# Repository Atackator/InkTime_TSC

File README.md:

InkTime-TSC Project

This project presents the design and development of a low-power, multi-functional smartwatch platform. The system is built around the nRF52840 SoC and integrates an E-paper display, motion sensing capabilities, and optimized power management within a compact PCB tailored for wearable devices.

### Bill of Materials (BOM) - PCB INKTIME

| Cant. | Referințe | Valoare | Capsulă | Descriere | MPN |
|:---:|:---|:---|:---|:---|:---|
| 1 | ANT1 | 2450AT18B100E | ANTC3216 | Antennas 2.45GHz | 2450AT18B100E |
| 4 | C1, C2, C17, C18 | 12pF | 0201 | Generic chip capacitor | - |
| 6 | C29, C30, C31, C32, C37, C38 | 1uF | 0201 | Generic chip capacitor | - |
| 1 | IC1 | BQ25180YBGR | 8-DSBGA | Charger IC Li-Ion | Texas Instruments |
| 1 | IC2 | DRV2605YZFR | 9-DSBGA | Haptic Driver | DRV2605YZFR |
| 1 | IC9 | RT6160AWSC | 15-WLCSP | Buck-Boost Regulator | RT6160AWSC |
| 1 | U1 | NRF52840_QF | AQFN-73 | nRF52840 SoC | - |
| 14 | TP1...TP_VREG | Test Point | TP20R | Test pads | - |

Hardware Overview
1. Core Processing Unit: nRF52840

The nRF52840 System-on-Chip serves as the central controller, chosen for its strong balance between computational performance and low energy consumption.

Main Characteristics:

ARM Cortex-M4F core with floating-point support
Native USB functionality
Flexible GPIO configuration supporting SPI and I2C interfaces

Clocking:

32 MHz external crystal for high-speed operation
32.768 kHz crystal for accurate timekeeping during low-power modes

Wireless Capability:

Integrated 2.4 GHz RF frontend paired with a ceramic antenna for Bluetooth Low Energy (BLE) communication
2. Power Management and Charging

The device includes a carefully designed power architecture to support portable operation.

USB-C Port:

Provides 5V input and data connectivity
Protected against electrostatic discharge using the USBLC6-2SC6Y

Battery Charging and Regulation:

BQ25180 handles LiPo charging and power path management
RT6160 DC/DC converter ensures efficient voltage regulation

Filtering and Stability:

LC filtering network reduces noise and stabilizes supply rails

Battery Monitoring:

MAX17048 fuel gauge communicates via I2C to estimate battery charge level accurately
3. E-Paper Display Module

A 1.54-inch E-paper display is used as the main visual interface, connected through a 24-pin FPC connector.

Driving Mechanism:

A custom boost circuit (using MOSFETs, Schottky diodes, and capacitors) generates the required high voltages

Communication:

SPI interface with dedicated control signals: DC (Data/Command), RST (Reset), and BUSY

Design Motivation:

The display retains the image without continuous power, making it ideal for always-on wearable applications
4. Motion Sensing and Haptic Feedback

IMU Sensor:

BMA421 accelerometer used for motion tracking
I2C communication interface
Interrupt pins (INT1, INT2) allow the MCU to wake on movement or gesture detection

Haptic System:

DRV2605 driver controls vibration feedback
Offloads waveform generation from the MCU for efficient operation
5. User Interface and Debugging

Buttons:

Three physical buttons (Up, Enter, Down) connected to GPIOs for navigation

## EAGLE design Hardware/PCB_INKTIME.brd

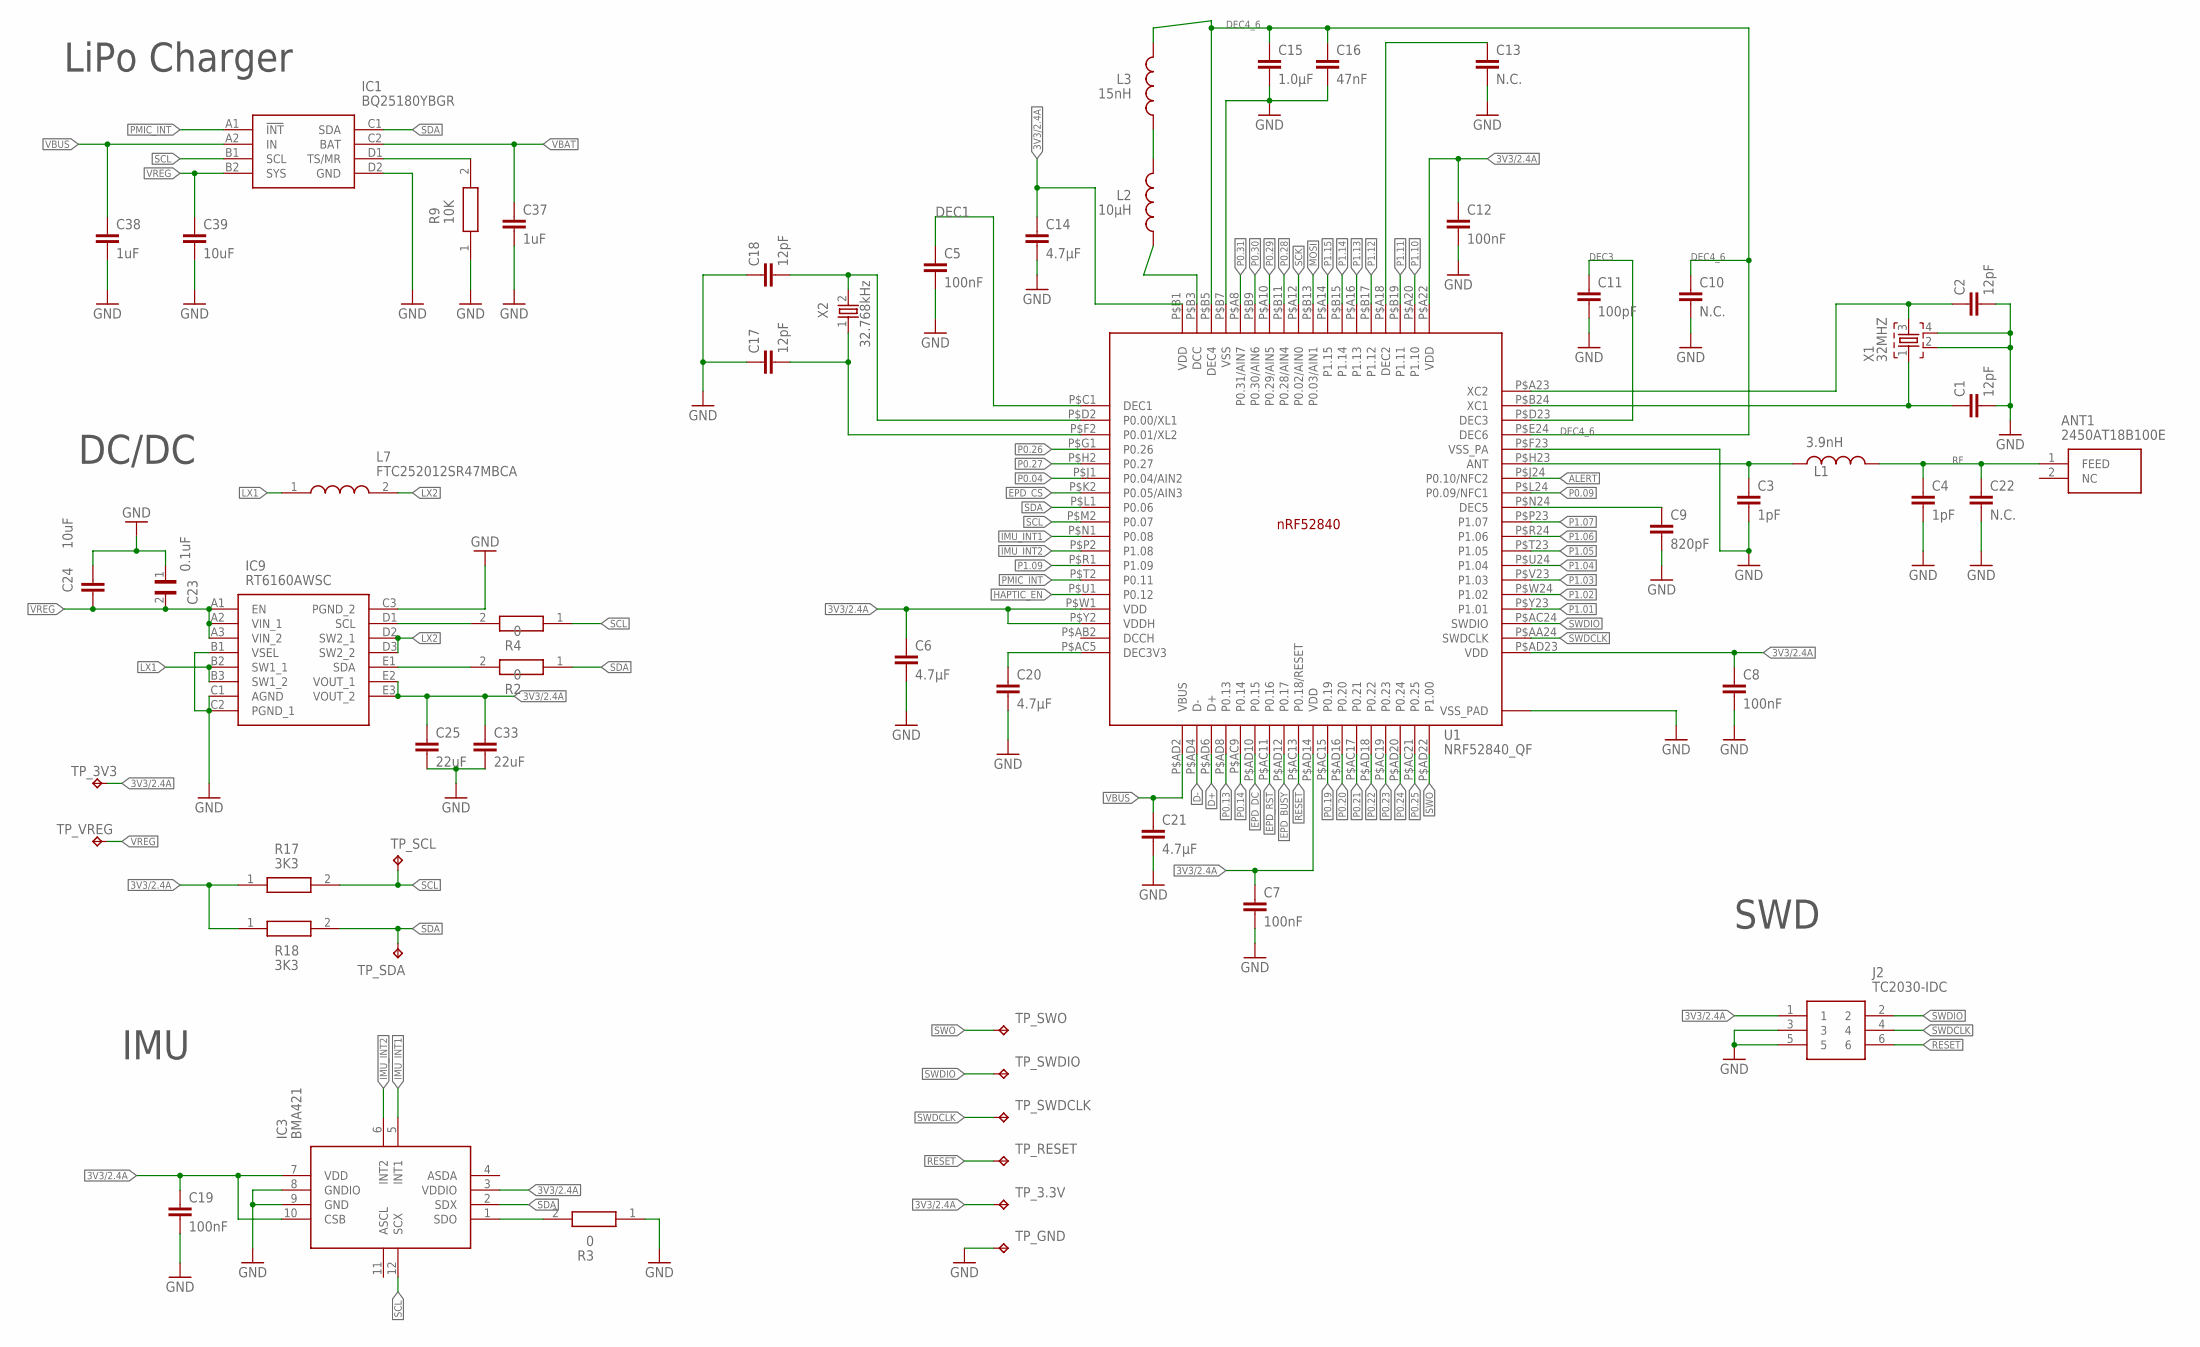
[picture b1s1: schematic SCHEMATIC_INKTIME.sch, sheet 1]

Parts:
ANT1: 2450AT18B100E; 2450AT18B100E_ANTC3216X140N
C1, C2, C17, C18: 12pF; NORDIC_NRF_3_RESC0201_L
C3, C4: 1pF; NORDIC_NRF_3_RESC0201_L
C5, C7, C8, C12, C19: 100nF; NORDIC_NRF_3_RESC0201_L
C6, C14, C20, C21: 4.7µF; NORDIC_NRF_3_RESC0402_L
C9: 820pF; NORDIC_NRF_3_RESC0201_L
C10, C13, C22: N.C.; NORDIC_NRF_3_RESC0201_L
C11: 100pF; NORDIC_NRF_3_RESC0201_L
C15: 1.0µF; NORDIC_NRF_3_RESC0402_L
C16: 47nF; NORDIC_NRF_3_RESC0201_L
C23: 0.1uF; GRM011R60J152KE01L_2_CAPC0201X13N
C24, C39: 10uF; NORDIC_NRF_3_RESC0402_L
C25, C33: 22uF; NORDIC_NRF_3_RESC0402_L
C37, C38: 1uF; NORDIC_NRF_3_RESC0402_L
IC1: BQ25180YBGR; BQ25180YBGR_BGA8C40P2X4_100X155X50
IC3: BMA421; BMA423_BMA423
IC9: RT6160AWSC; RT6160AWSC_BGA15C40P3X5_140X230X60
J2: TC2030-IDC; TC2030-IDC_TC2030IDC
L1: 3.9nH; NORDIC_NRF_2_RESC0402_L
L2: 10µH; NORDIC_NRF_2_RESC0402_L
L3: 15nH; NORDIC_NRF_2_RESC0402_L
L7: FTC252012SR47MBCA; MLP2016SR47MT0S1_INDC2016X100N
R2, R3, R4: 0; CPF0201D7K68C1_0201
R9: 10K; CPF0201D7K68C1_0201
R17, R18: 3K3; CPF0201D7K68C1_0201
TP_3.3V, TP_3V3: HECTOR_WATCH_1_TPTP20R; HECTOR_WATCH_1_TP20R
TP_GND: HECTOR_WATCH_1_TPTP20R; HECTOR_WATCH_1_TP20R
TP_RESET: HECTOR_WATCH_1_TPTP20R; HECTOR_WATCH_1_TP20R
TP_SCL: HECTOR_WATCH_1_TPTP20R; HECTOR_WATCH_1_TP20R
TP_SDA: HECTOR_WATCH_1_TPTP20R; HECTOR_WATCH_1_TP20R
TP_SWDCLK: HECTOR_WATCH_1_TPTP20R; HECTOR_WATCH_1_TP20R
TP_SWDIO: HECTOR_WATCH_1_TPTP20R; HECTOR_WATCH_1_TP20R
TP_SWO: HECTOR_WATCH_1_TPTP20R; HECTOR_WATCH_1_TP20R
TP_VREG: HECTOR_WATCH_1_TPTP20R; HECTOR_WATCH_1_TP20R
U1: NRF52840_QF; NORDIC_NRF_4_AQFN50P700X700X85_HS-74N
X1: 32MHZ; NORDIC_NRF_BT-XTAL_2016_N
X2: 32.768kHz; NORDIC_NRF_1_XTAL_3215_N

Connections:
3V3/2.4A: C6.1, C7.1, C8.1, C12.1, C14.1, C19.1, C25.1, C33.1, IC3.3 (VDDIO), IC3.7 (VDD), IC3.10 (CSB), IC9.E2 (VOUT_1), IC9.E3 (VOUT_2), J2.1, R17.1, R18.1, TP_3.3V.TP, TP_3V3.TP, U1.P$A22 (VDD), U1.P$AD14 (VDD), U1.P$AD23 (VDD), U1.P$B1 (VDD), U1.P$W1 (VDD), U1.P$Y2 (VDDH); also elsewhere on the board
ALERT: U1.P$J24 (P0.10/NFC2); also elsewhere on the board
D+: U1.P$AD6 (D+); also elsewhere on the board
D-: U1.P$AD4 (D-); also elsewhere on the board
DEC1: C5.1, U1.P$C1 (DEC1)
DEC3: C11.1, U1.P$D23 (DEC3)
DEC4_6: C10.1, C15.1, C16.1, L3.2, U1.P$B5 (DEC4), U1.P$E24 (DEC6)
EPD_BUSY: U1.P$AD12 (P0.17); also elsewhere on the board
EPD_CS: U1.P$K2 (P0.05/AIN3); also elsewhere on the board
EPD_DC: U1.P$AD10 (P0.15); also elsewhere on the board
EPD_RST: U1.P$AC11 (P0.16); also elsewhere on the board
GND: C1.2, C2.2, C3.2, C4.2, C5.2, C6.2, C7.2, C8.2, C9.2, C10.2, C11.2, C12.2, C13.2, C14.2, C15.2, C16.2, C17.1, C18.1, C19.2, C20.2, C21.2, C22.2, C23.1, C24.1, C25.2, C33.2, C37.2, C38.2, C39.2, IC1.D2 (GND), IC3.8 (GNDIO), IC3.9 (GND), IC9.B1 (VSEL), IC9.C1 (AGND), IC9.C2 (PGND_1), IC9.C3 (PGND_2), J2.3, J2.5, R3.1, R9.1, TP_GND.TP, U1.P$74 (VSS_PAD), U1.P$75 (VSS_PAD), U1.P$76 (VSS_PAD), U1.P$77 (VSS_PAD), U1.P$78 (VSS_PAD), U1.P$79 (VSS_PAD), U1.P$80 (VSS_PAD), U1.P$81 (VSS_PAD), U1.P$82 (VSS_PAD), U1.P$83 (VSS_PAD), U1.P$84 (VSS_PAD), U1.P$85 (VSS_PAD), U1.P$86 (VSS_PAD), U1.P$87 (VSS_PAD), U1.P$88 (VSS_PAD), U1.P$89 (VSS_PAD), U1.P$90 (VSS_PAD), U1.P$B7 (VSS), U1.P$F23 (VSS_PA), X1.2, X1.4; also elsewhere on the board
HAPTIC_EN: U1.P$U1 (P0.12); also elsewhere on the board
IMU_INT1: IC3.5 (INT1), U1.P$N1 (P0.08)
IMU_INT2: IC3.6 (INT2), U1.P$P2 (P1.08)
LX1: IC9.B2 (SW1_1), IC9.B3 (SW1_2), L7.1
LX2: IC9.D2 (SW2_1), IC9.D3 (SW2_2), L7.2
MOSI: U1.P$B13 (P0.03/AIN1); also elsewhere on the board
unnamed: IC1.D1 (TS/MR), R9.2
unnamed: C18.2, U1.P$D2 (P0.00/XL1), X2.2
unnamed: C1.1, U1.P$B24 (XC1), X1.1
unnamed: C2.1, U1.P$A23 (XC2), X1.3
unnamed: C17.2, U1.P$F2 (P0.01/XL2), X2.1
unnamed: L2.2, L3.1
unnamed: L2.1, U1.P$B3 (DCC)
unnamed: C9.1, U1.P$N24 (DEC5)
unnamed: C13.1, U1.P$A18 (DEC2)
unnamed: C3.1, L1.1, U1.P$H23 (ANT)
unnamed: C20.1, U1.P$AC5 (DEC3V3)
unnamed 35: IC3.1 (SDO), R3.2; also elsewhere on the board
unnamed: IC9.E1 (SDA), R2.2
unnamed: IC9.D1 (SCL), R4.2
P0.04: U1.P$J1 (P0.04/AIN2)
P0.09: U1.P$L24 (P0.09/NFC1)
P0.13: U1.P$AD8 (P0.13); also elsewhere on the board
P0.14: U1.P$AC9 (P0.14); also elsewhere on the board
P0.19: U1.P$AC15 (P0.19)
P0.20: U1.P$AD16 (P0.20)
P0.21: U1.P$AC17 (P0.21)
P0.22: U1.P$AD18 (P0.22)
P0.23: U1.P$AC19 (P0.23)
P0.24: U1.P$AD20 (P0.24)
P0.25: U1.P$AC21 (P0.25)
P0.26: U1.P$G1 (P0.26)
P0.27: U1.P$H2 (P0.27)
P0.28: U1.P$B11 (P0.28/AIN4)
P0.29: U1.P$A10 (P0.29/AIN5)
P0.30: U1.P$B9 (P0.30/AIN6)
P0.31: U1.P$A8 (P0.31/AIN7)
P1.01: U1.P$Y23 (P1.01); also elsewhere on the board
P1.02: U1.P$W24 (P1.02); also elsewhere on the board
P1.03: U1.P$V23 (P1.03)
P1.04: U1.P$U24 (P1.04)
P1.05: U1.P$T23 (P1.05)
P1.06: U1.P$R24 (P1.06)
P1.07: U1.P$P23 (P1.07)
P1.09: U1.P$R1 (P1.09)
P1.10: U1.P$A20 (P1.10)
P1.11: U1.P$B19 (P1.11)
P1.12: U1.P$B17 (P1.12)
P1.13: U1.P$A16 (P1.13)
P1.14: U1.P$B15 (P1.14)
P1.15: U1.P$A14 (P1.15)
PMIC_INT: IC1.A1 (!INT), U1.P$T2 (P0.11)
RESET: J2.6, TP_RESET.TP, U1.P$AC13 (P0.18/RESET)
RF: ANT1.1 (FEED), C4.1, C22.1, L1.2
SCK: U1.P$A12 (P0.02/AIN0); also elsewhere on the board
SCL: IC1.B1 (SCL), IC3.12 (SCX), R4.1, R17.2, TP_SCL.TP, U1.P$M2 (P0.07); also elsewhere on the board
SDA: IC1.C1 (SDA), IC3.2 (SDX), R2.1, R18.2, TP_SDA.TP, U1.P$L1 (P0.06); also elsewhere on the board
SWDCLK: J2.4, TP_SWDCLK.TP, U1.P$AA24 (SWDCLK)
SWDIO: J2.2, TP_SWDIO.TP, U1.P$AC24 (SWDIO)
SWO: TP_SWO.TP, U1.P$AD22 (P1.00)
VBAT: C37.1, IC1.C2 (BAT); also elsewhere on the board
VBUS: C21.1, C38.1, IC1.A2 (IN), U1.P$AD2 (VBUS); also elsewhere on the board
VREG: C23.2, C24.2, C39.1, IC1.B2 (SYS), IC9.A1 (EN), IC9.A2 (VIN_1), IC9.A3 (VIN_2), TP_VREG.TP

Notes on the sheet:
LiPo Charger
DC/DC
IMU
SWD

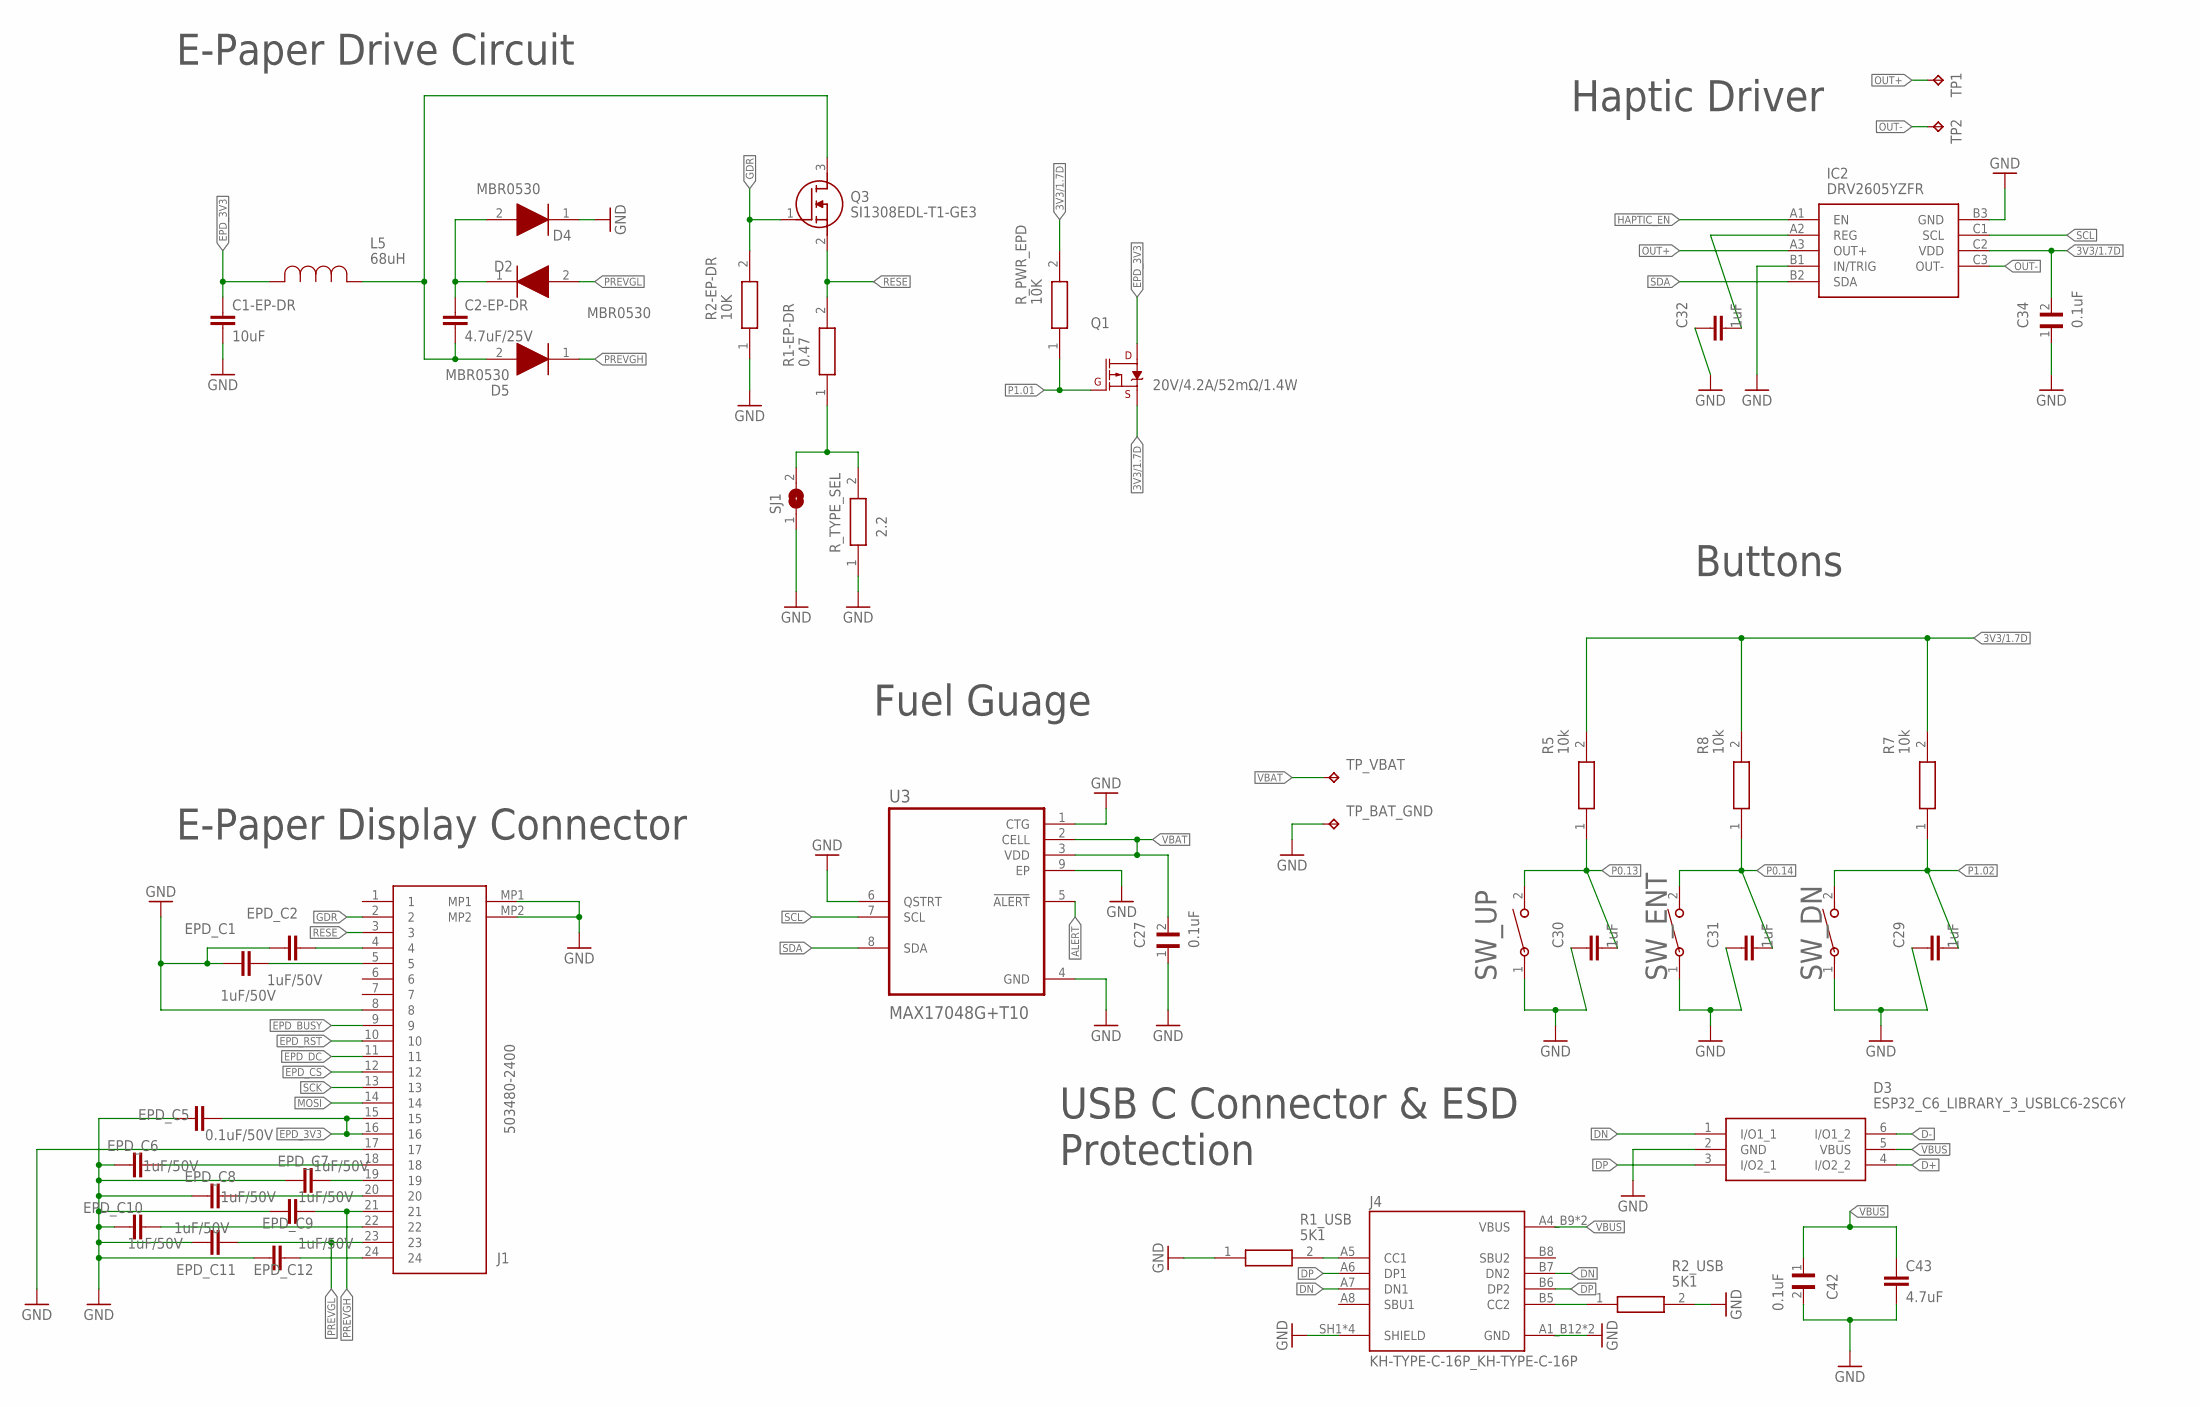
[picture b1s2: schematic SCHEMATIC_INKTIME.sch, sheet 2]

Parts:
C1-EP-DR: 10uF; NORDIC_NRF_3_RESC0402_L
C2-EP-DR: 4.7uF/25V; NORDIC_NRF_3_RESC0402_L
C27, C34, C42: 0.1uF; GRM011R60J152KE01L_2_CAPC0201X13N
C29, C30, C31, C32: 1uF; NORDIC_NRF_3_RESC0402_L
C43: 4.7uF; NORDIC_NRF_3_RESC0402_L
D2, D4, D5: MBR0530; ESP32_C6_LIBRARY_5_SOD3716X135N
D3: ESP32_C6_LIBRARY_3_USBLC6-2SC6Y; ESP32_C6_LIBRARY_3_SOT95P280X145-6N
EPD_C1, EPD_C2, EPD_C6, EPD_C7, EPD_C8, EPD_C9, EPD_C10, EPD_C11, EPD_C12: 1uF/50V; NORDIC_NRF_3_RESC0402_L
EPD_C5: 0.1uF/50V; NORDIC_NRF_3_RESC0201_L
IC2: DRV2605YZFR; DRV2605YZFR_BGA9C50P3X3_144X144X62
J1: 503480-2400; 503480-2400_5034802400
J4: KH-TYPE-C-16P_KH-TYPE-C-16P; KH-TYPE-C-16P_KINGHELM_KH-TYPE-C-16P
L5: 68uH; ESP32_C6_LIBRARY_2_IND_4828-WE-TPC_WRE
Q1: 20V/4.2A/52mΩ/1.4W; ESP32_C6_LIBRARY_4_ESP32_C6_LIBRARY_4_ESP32_C6_LIBRARY_4_ES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
Q3: SI1308EDL-T1-GE3; ESP32_C6_LIBRARY_6_SOT65P210X110-3N
R1-EP-DR: 0.47; CPF0201D7K68C1_0201
R1_USB, R2_USB: 5K1; CPF0201D7K68C1_0201
R2-EP-DR: 10K; CPF0201D7K68C1_0201
R5, R7, R8: 10k; CPF0201D7K68C1_0201
R_PWR_EPD: 10K; CPF0201D7K68C1_0201
R_TYPE_SEL: 2.2; CPF0201D7K68C1_0201
SJ1: ESP32_C6_LIBRARY_7_JUMPER_SJ
SW_DN: 2025-10-22_07-23-44_LIBRARY_EVP-AKE31ASW_EVP-AKE3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; 2025-10-22_07-23-44_LIBRARY_SW_EVP-AKE31A_PAN
SW_ENT: 2025-10-22_07-23-44_LIBRARY_EVP-AKE31ASW_EVP-AKE3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; 2025-10-22_07-23-44_LIBRARY_SW_EVP-AKE31A_PAN
SW_UP: 2025-10-22_07-23-44_LIBRARY_EVP-AKE31ASW_EVP-AKE3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; 2025-10-22_07-23-44_LIBRARY_SW_EVP-AKE31A_PAN
TP1, TP2: HECTOR_WATCH_1_TPTP20R; HECTOR_WATCH_1_TP20R
TP_BAT_GND: HECTOR_WATCH_1_TPTP20R; HECTOR_WATCH_1_TP20R
TP_VBAT: HECTOR_WATCH_1_TPTP20R; HECTOR_WATCH_1_TP20R
U3: MAX17048G+T10; ESP32_C6_LIBRARY_SON50P200X200X80-9N

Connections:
3V3/1.7D: C34.2, IC2.C2 (VDD), Q1.2 (S), R5.2, R7.2, R8.2, R_PWR_EPD.2
ALERT: U3.5 (!ALERT); also elsewhere on the board
D+: D3.4 (I/O2_2); also elsewhere on the board
D-: D3.6 (I/O1_2); also elsewhere on the board
DN: D3.1 (I/O1_1), J4.A7 (DN1), J4.B7 (DN2)
DP: D3.3 (I/O2_1), J4.A6 (DP1), J4.B6 (DP2)
EPD_3V3: C1-EP-DR.1, EPD_C5.2, J1.15, J1.16, L5.2, Q1.3 (D); also elsewhere on the board
EPD_BUSY: J1.9; also elsewhere on the board
EPD_CS: J1.12; also elsewhere on the board
EPD_DC: J1.11; also elsewhere on the board
EPD_RST: J1.10; also elsewhere on the board
GDR: J1.2, Q3.1 (G), R2-EP-DR.2
GND: C1-EP-DR.2, C27.1, C29.1, C30.1, C31.1, C32.1, C34.1, C42.2, C43.2, D3.2 (GND), D4.1 (K), EPD_C1.1, EPD_C2.1, EPD_C5.1, EPD_C6.1, EPD_C7.1, EPD_C8.1, EPD_C9.1, EPD_C10.1, EPD_C11.1, EPD_C12.1, IC2.B1 (IN/TRIG), IC2.B3 (GND), J1.8, J1.17, J1.MP1, J1.MP2, J4.A1_B12 (GND), J4.A12_B1 (GND), J4.SH1 (SHIELD), J4.SH2 (SHIELD), J4.SH3 (SHIELD), J4.SH4 (SHIELD), R1_USB.1, R2-EP-DR.1, R2_USB.2, R_TYPE_SEL.1, SJ1.1, SW_DN.1, SW_ENT.1, SW_UP.1, TP_BAT_GND.TP, U3.1 (CTG), U3.4 (GND), U3.6 (QSTRT), U3.9 (EP); also elsewhere on the board
HAPTIC_EN: IC2.A1 (EN); also elsewhere on the board
MOSI: J1.14; also elsewhere on the board
unnamed: C32.2, IC2.A2 (REG)
unnamed 36: C2-EP-DR.2, D5.2 (A), L5.1, Q3.3 (D); also elsewhere on the board
unnamed: C2-EP-DR.1, D2.1 (K), D4.2 (A)
unnamed: J4.A5 (CC1), R1_USB.2
unnamed: EPD_C2.2, J1.4
unnamed: R1-EP-DR.1, R_TYPE_SEL.2, SJ1.2
unnamed: EPD_C1.2, J1.5
unnamed: J4.B5 (CC2), R2_USB.1
unnamed: EPD_C6.2, J1.18
unnamed: EPD_C7.2, J1.19
unnamed: EPD_C8.2, J1.20
unnamed: EPD_C10.2, J1.22
unnamed: EPD_C12.2, J1.24
OUT+: IC2.A3 (OUT+), TP1.TP
OUT-: IC2.C3 (OUT-), TP2.TP
P0.13: C30.2, R5.1, SW_UP.2; also elsewhere on the board
P0.14: C31.2, R8.1, SW_ENT.2; also elsewhere on the board
P1.01: Q1.1 (G), R_PWR_EPD.1; also elsewhere on the board
P1.02: C29.2, R7.1, SW_DN.2; also elsewhere on the board
PREVGH: D5.1 (K), EPD_C9.2, J1.21
PREVGL: D2.2 (A), EPD_C11.2, J1.23
RESE: J1.3, Q3.2 (S), R1-EP-DR.2
SCK: J1.13; also elsewhere on the board
SCL: IC2.C1 (SCL), U3.7 (SCL); also elsewhere on the board
SDA: IC2.B2 (SDA), U3.8 (SDA); also elsewhere on the board
VBAT: C27.2, TP_VBAT.TP, U3.2 (CELL), U3.3 (VDD); also elsewhere on the board
VBUS: C42.1, C43.1, D3.5 (VBUS), J4.A4_B9 (VBUS), J4.A9_B4 (VBUS); also elsewhere on the board

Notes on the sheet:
E-Paper Drive Circuit
E-Paper Display Connector
Fuel Guage
Buttons
Haptic Driver
USB C Connector & ESD Protection

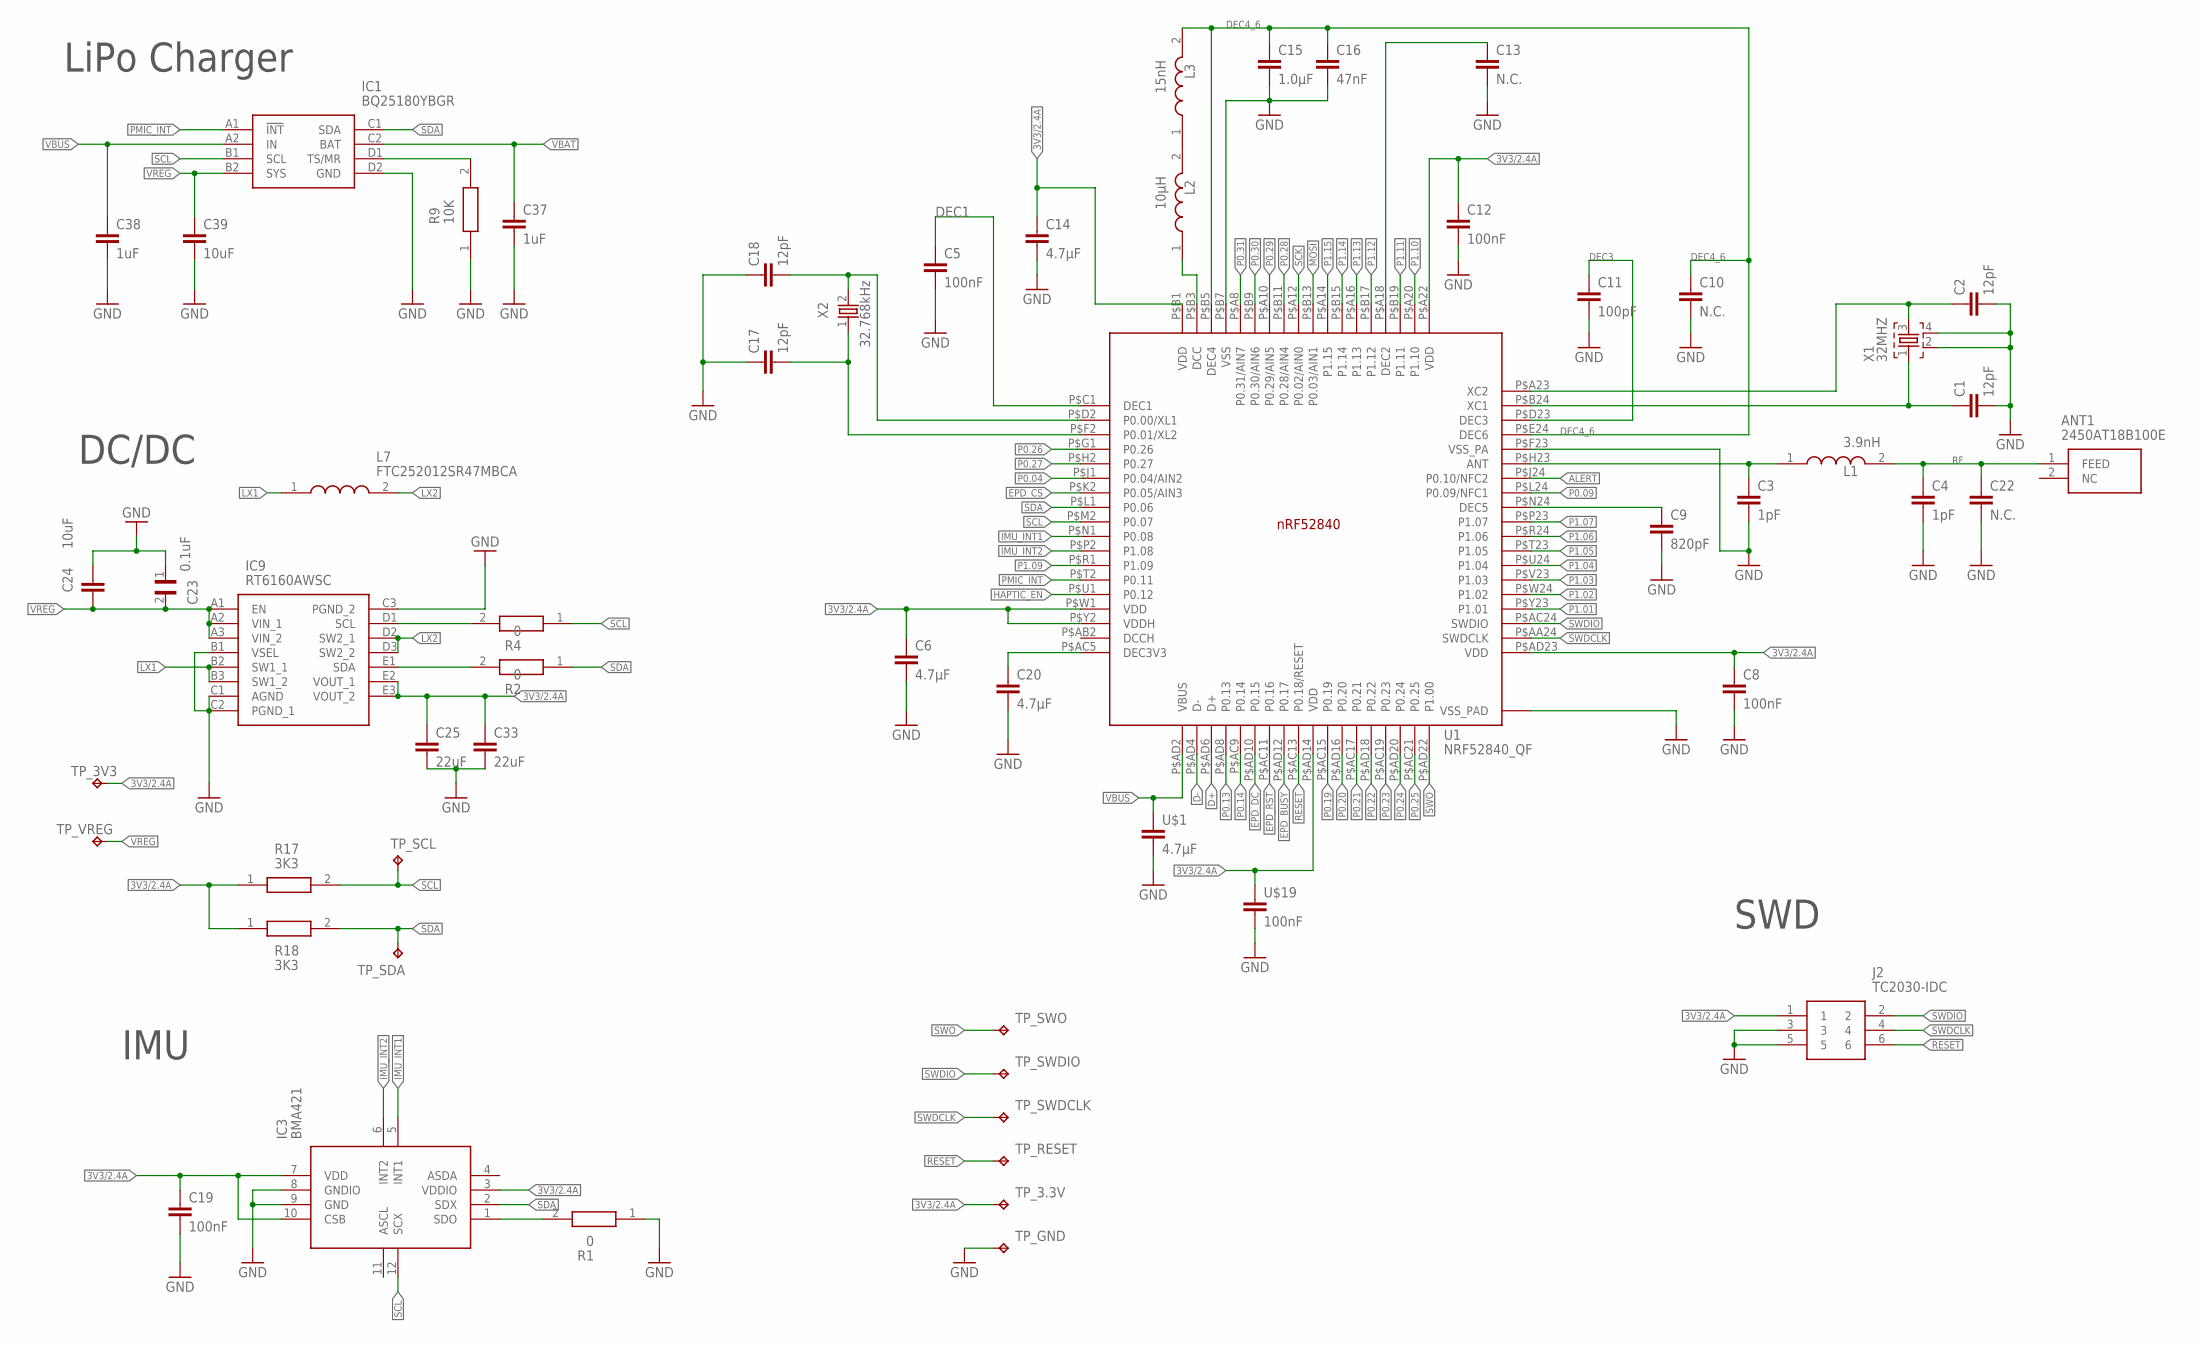
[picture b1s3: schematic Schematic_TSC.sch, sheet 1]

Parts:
ANT1: 2450AT18B100E; 2450AT18B100E_ANTC3216X140N
C1, C2, C17, C18: 12pF; NORDIC_NRF_3_RESC0201_L
C3, C4: 1pF; NORDIC_NRF_3_RESC0201_L
C5, C8, C12, C19: 100nF; NORDIC_NRF_3_RESC0201_L
C6, C14, C20: 4.7µF; NORDIC_NRF_3_RESC0201_L
C9: 820pF; NORDIC_NRF_3_RESC0201_L
C10, C13, C22: N.C.; NORDIC_NRF_3_RESC0201_L
C11: 100pF; NORDIC_NRF_3_RESC0201_L
C15: 1.0µF; NORDIC_NRF_3_RESC0201_L
C16: 47nF; NORDIC_NRF_3_RESC0201_L
C23: 0.1uF; GRM011R60J152KE01L_2_CAPC0201X13N
C24, C39: 10uF; NORDIC_NRF_3_RESC0201_L
C25, C33: 22uF; NORDIC_NRF_3_RESC0201_L
C37, C38: 1uF; NORDIC_NRF_3_RESC0201_L
IC1: BQ25180YBGR; BQ25180YBGR_BGA8C40P2X4_100X155X50
IC3: BMA421; BMA423_BMA423
IC9: RT6160AWSC; RT6160AWSC_BGA15C40P3X5_140X230X60
J2: TC2030-IDC; TC2030-IDC_TC2030IDC
L1: 3.9nH; MLP2016SR47MT0S1_INDC2016X100N
L2: 10µH; MLP2016SR47MT0S1_INDC2016X100N
L3: 15nH; MLP2016SR47MT0S1_INDC2016X100N
L7: FTC252012SR47MBCA; MLP2016SR47MT0S1_INDC2016X100N
R1, R2, R4: 0; CPF0201D7K68C1_0201
R9: 10K; CPF0201D7K68C1_0201
R17, R18: 3K3; CPF0201D7K68C1_0201
TP_3.3V, TP_3V3: HECTOR_WATCH_1_TPTP20R; HECTOR_WATCH_1_TP20R
TP_GND: HECTOR_WATCH_1_TPTP20R; HECTOR_WATCH_1_TP20R
TP_RESET: HECTOR_WATCH_1_TPTP20R; HECTOR_WATCH_1_TP20R
TP_SCL: HECTOR_WATCH_1_TPTP20R; HECTOR_WATCH_1_TP20R
TP_SDA: HECTOR_WATCH_1_TPTP20R; HECTOR_WATCH_1_TP20R
TP_SWDCLK: HECTOR_WATCH_1_TPTP20R; HECTOR_WATCH_1_TP20R
TP_SWDIO: HECTOR_WATCH_1_TPTP20R; HECTOR_WATCH_1_TP20R
TP_SWO: HECTOR_WATCH_1_TPTP20R; HECTOR_WATCH_1_TP20R
TP_VREG: HECTOR_WATCH_1_TPTP20R; HECTOR_WATCH_1_TP20R
U1: NRF52840_QF; NORDIC_NRF_4_AQFN50P700X700X85_HS-74N
U$1: 4.7µF; NORDIC_NRF_3_RESC0201_L
U$19: 100nF; NORDIC_NRF_3_RESC0201_L
X1: 32MHZ; NORDIC_NRF_BT-XTAL_2016_N
X2: 32.768kHz; NORDIC_NRF_1_XTAL_3215_N

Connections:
3V3/2.4A: C6.1, C8.1, C12.1, C14.1, C19.1, C25.1, C33.1, IC3.3 (VDDIO), IC3.7 (VDD), IC3.10 (CSB), IC9.E2 (VOUT_1), IC9.E3 (VOUT_2), J2.1, R17.1, R18.1, TP_3.3V.TP, TP_3V3.TP, U1.P$A22 (VDD), U1.P$AD14 (VDD), U1.P$AD23 (VDD), U1.P$B1 (VDD), U1.P$W1 (VDD), U1.P$Y2 (VDDH), U$19.1; also elsewhere on the board
ALERT: U1.P$J24 (P0.10/NFC2); also elsewhere on the board
D+: U1.P$AD6 (D+); also elsewhere on the board
D-: U1.P$AD4 (D-); also elsewhere on the board
DEC1: C5.1, U1.P$C1 (DEC1)
DEC3: C11.1, U1.P$D23 (DEC3)
DEC4_6: C10.1, C15.1, C16.1, L3.2, U1.P$B5 (DEC4), U1.P$E24 (DEC6)
EPD_BUSY: U1.P$AD12 (P0.17); also elsewhere on the board
EPD_CS: U1.P$K2 (P0.05/AIN3); also elsewhere on the board
EPD_DC: U1.P$AD10 (P0.15); also elsewhere on the board
EPD_RST: U1.P$AC11 (P0.16); also elsewhere on the board
GND: C1.2, C2.2, C3.2, C4.2, C5.2, C6.2, C8.2, C9.2, C10.2, C11.2, C12.2, C13.2, C14.2, C15.2, C16.2, C17.1, C18.1, C19.2, C20.2, C22.2, C23.1, C24.1, C25.2, C33.2, C37.2, C38.2, C39.2, IC1.D2 (GND), IC3.8 (GNDIO), IC3.9 (GND), IC9.B1 (VSEL), IC9.C1 (AGND), IC9.C2 (PGND_1), IC9.C3 (PGND_2), J2.3, J2.5, R1.1, R9.1, TP_GND.TP, U1.P$74 (VSS_PAD), U1.P$75 (VSS_PAD), U1.P$76 (VSS_PAD), U1.P$77 (VSS_PAD), U1.P$78 (VSS_PAD), U1.P$79 (VSS_PAD), U1.P$80 (VSS_PAD), U1.P$81 (VSS_PAD), U1.P$82 (VSS_PAD), U1.P$83 (VSS_PAD), U1.P$84 (VSS_PAD), U1.P$85 (VSS_PAD), U1.P$86 (VSS_PAD), U1.P$87 (VSS_PAD), U1.P$88 (VSS_PAD), U1.P$89 (VSS_PAD), U1.P$90 (VSS_PAD), U1.P$B7 (VSS), U1.P$F23 (VSS_PA), U$1.2, U$19.2, X1.2, X1.4; also elsewhere on the board
HAPTIC_EN: U1.P$U1 (P0.12); also elsewhere on the board
IMU_INT1: IC3.5 (INT1), U1.P$N1 (P0.08)
IMU_INT2: IC3.6 (INT2), U1.P$P2 (P1.08)
LX1: IC9.B2 (SW1_1), IC9.B3 (SW1_2), L7.1
LX2: IC9.D2 (SW2_1), IC9.D3 (SW2_2), L7.2
MOSI: U1.P$B13 (P0.03/AIN1); also elsewhere on the board
unnamed: IC1.D1 (TS/MR), R9.2
unnamed: C18.2, U1.P$D2 (P0.00/XL1), X2.2
unnamed: C1.1, U1.P$B24 (XC1), X1.1
unnamed: C2.1, U1.P$A23 (XC2), X1.3
unnamed: C17.2, U1.P$F2 (P0.01/XL2), X2.1
unnamed: L2.2, L3.1
unnamed: L2.1, U1.P$B3 (DCC)
unnamed: C9.1, U1.P$N24 (DEC5)
unnamed: C13.1, U1.P$A18 (DEC2)
unnamed: C3.1, L1.1, U1.P$H23 (ANT)
unnamed: C20.1, U1.P$AC5 (DEC3V3)
unnamed 35: IC3.1 (SDO), R1.2; also elsewhere on the board
unnamed: IC9.E1 (SDA), R2.2
unnamed: IC9.D1 (SCL), R4.2
P0.04: U1.P$J1 (P0.04/AIN2)
P0.09: U1.P$L24 (P0.09/NFC1)
P0.13: U1.P$AD8 (P0.13); also elsewhere on the board
P0.14: U1.P$AC9 (P0.14); also elsewhere on the board
P0.19: U1.P$AC15 (P0.19)
P0.20: U1.P$AD16 (P0.20)
P0.21: U1.P$AC17 (P0.21)
P0.22: U1.P$AD18 (P0.22)
P0.23: U1.P$AC19 (P0.23)
P0.24: U1.P$AD20 (P0.24)
P0.25: U1.P$AC21 (P0.25)
P0.26: U1.P$G1 (P0.26)
P0.27: U1.P$H2 (P0.27)
P0.28: U1.P$B11 (P0.28/AIN4)
P0.29: U1.P$A10 (P0.29/AIN5)
P0.30: U1.P$B9 (P0.30/AIN6)
P0.31: U1.P$A8 (P0.31/AIN7)
P1.01: U1.P$Y23 (P1.01); also elsewhere on the board
P1.02: U1.P$W24 (P1.02); also elsewhere on the board
P1.03: U1.P$V23 (P1.03)
P1.04: U1.P$U24 (P1.04)
P1.05: U1.P$T23 (P1.05)
P1.06: U1.P$R24 (P1.06)
P1.07: U1.P$P23 (P1.07)
P1.09: U1.P$R1 (P1.09)
P1.10: U1.P$A20 (P1.10)
P1.11: U1.P$B19 (P1.11)
P1.12: U1.P$B17 (P1.12)
P1.13: U1.P$A16 (P1.13)
P1.14: U1.P$B15 (P1.14)
P1.15: U1.P$A14 (P1.15)
PMIC_INT: IC1.A1 (!INT), U1.P$T2 (P0.11)
RESET: J2.6, TP_RESET.TP, U1.P$AC13 (P0.18/RESET)
RF: ANT1.1 (FEED), C4.1, C22.1, L1.2
SCK: U1.P$A12 (P0.02/AIN0); also elsewhere on the board
SCL: IC1.B1 (SCL), IC3.12 (SCX), R4.1, R17.2, TP_SCL.TP, U1.P$M2 (P0.07); also elsewhere on the board
SDA: IC1.C1 (SDA), IC3.2 (SDX), R2.1, R18.2, TP_SDA.TP, U1.P$L1 (P0.06); also elsewhere on the board
SWDCLK: J2.4, TP_SWDCLK.TP, U1.P$AA24 (SWDCLK)
SWDIO: J2.2, TP_SWDIO.TP, U1.P$AC24 (SWDIO)
SWO: TP_SWO.TP, U1.P$AD22 (P1.00)
VBAT: C37.1, IC1.C2 (BAT); also elsewhere on the board
VBUS: C38.1, IC1.A2 (IN), U1.P$AD2 (VBUS), U$1.1; also elsewhere on the board
VREG: C23.2, C24.2, C39.1, IC1.B2 (SYS), IC9.A1 (EN), IC9.A2 (VIN_1), IC9.A3 (VIN_2), TP_VREG.TP

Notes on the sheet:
LiPo Charger
DC/DC
IMU
SWD

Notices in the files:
parts and their libraries:
COPYRIGHT: Copyright (C) 2024 Ultra Librarian. All rights reserved.
COPYRIGHT: Copyright (C) 2025 Ultra Librarian. All rights reserved.
